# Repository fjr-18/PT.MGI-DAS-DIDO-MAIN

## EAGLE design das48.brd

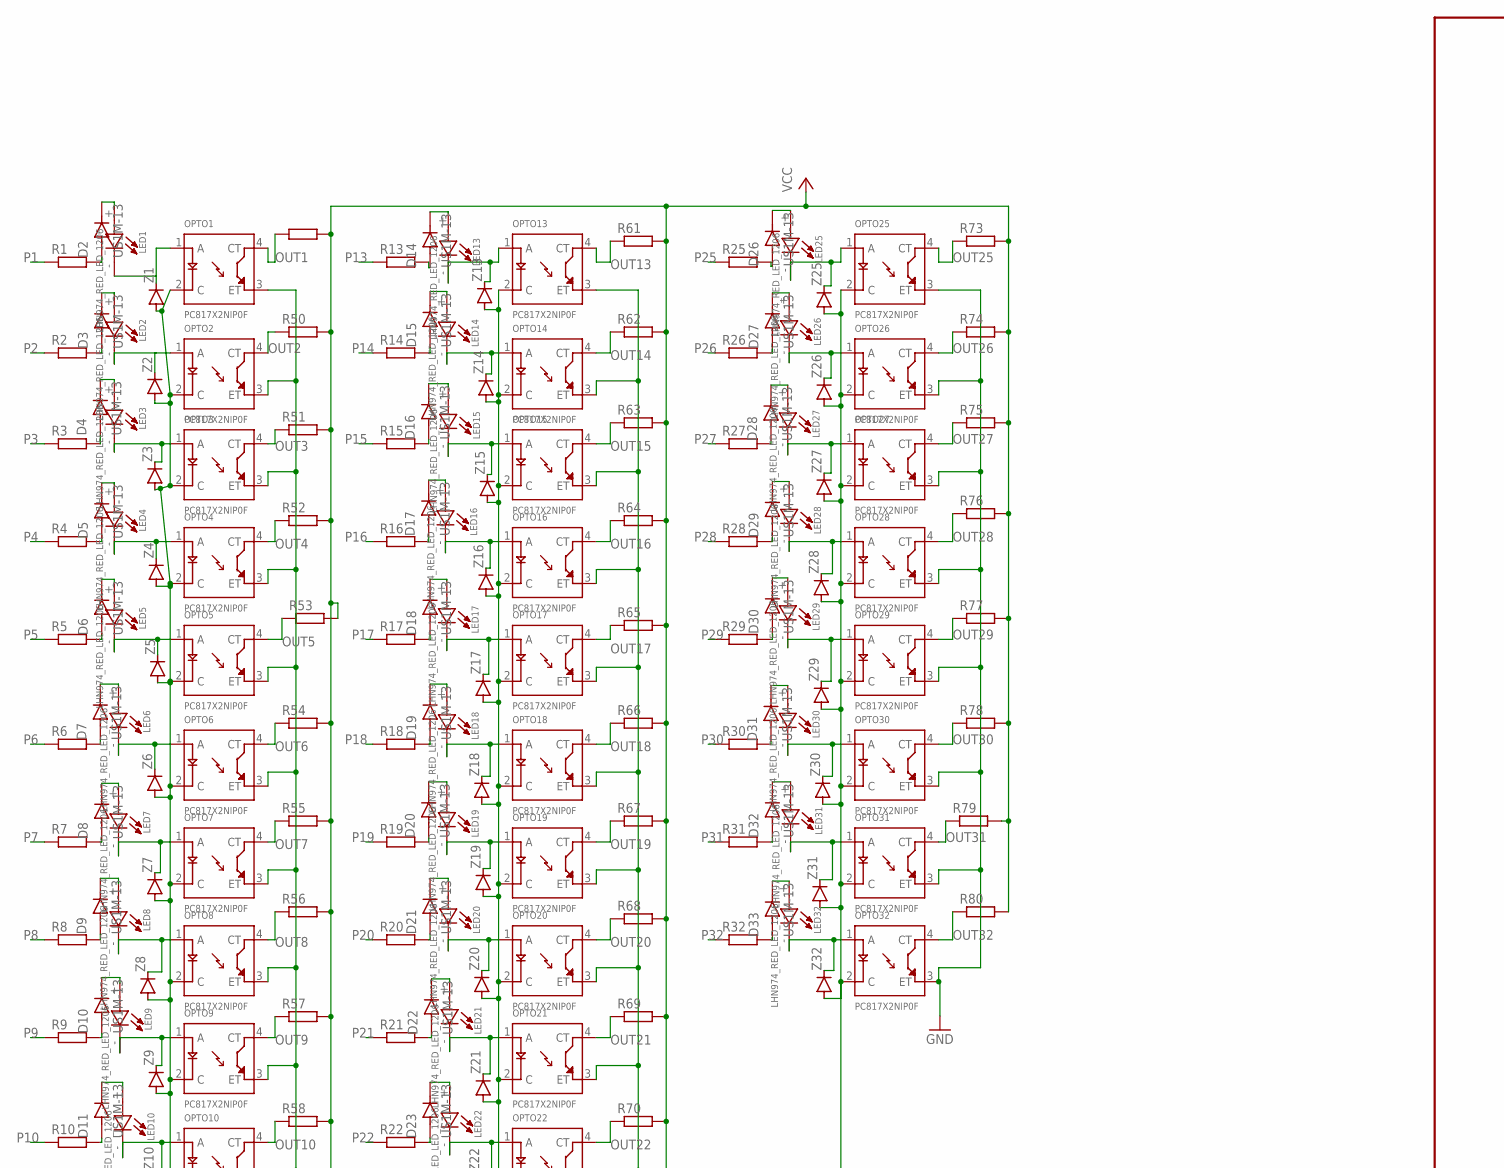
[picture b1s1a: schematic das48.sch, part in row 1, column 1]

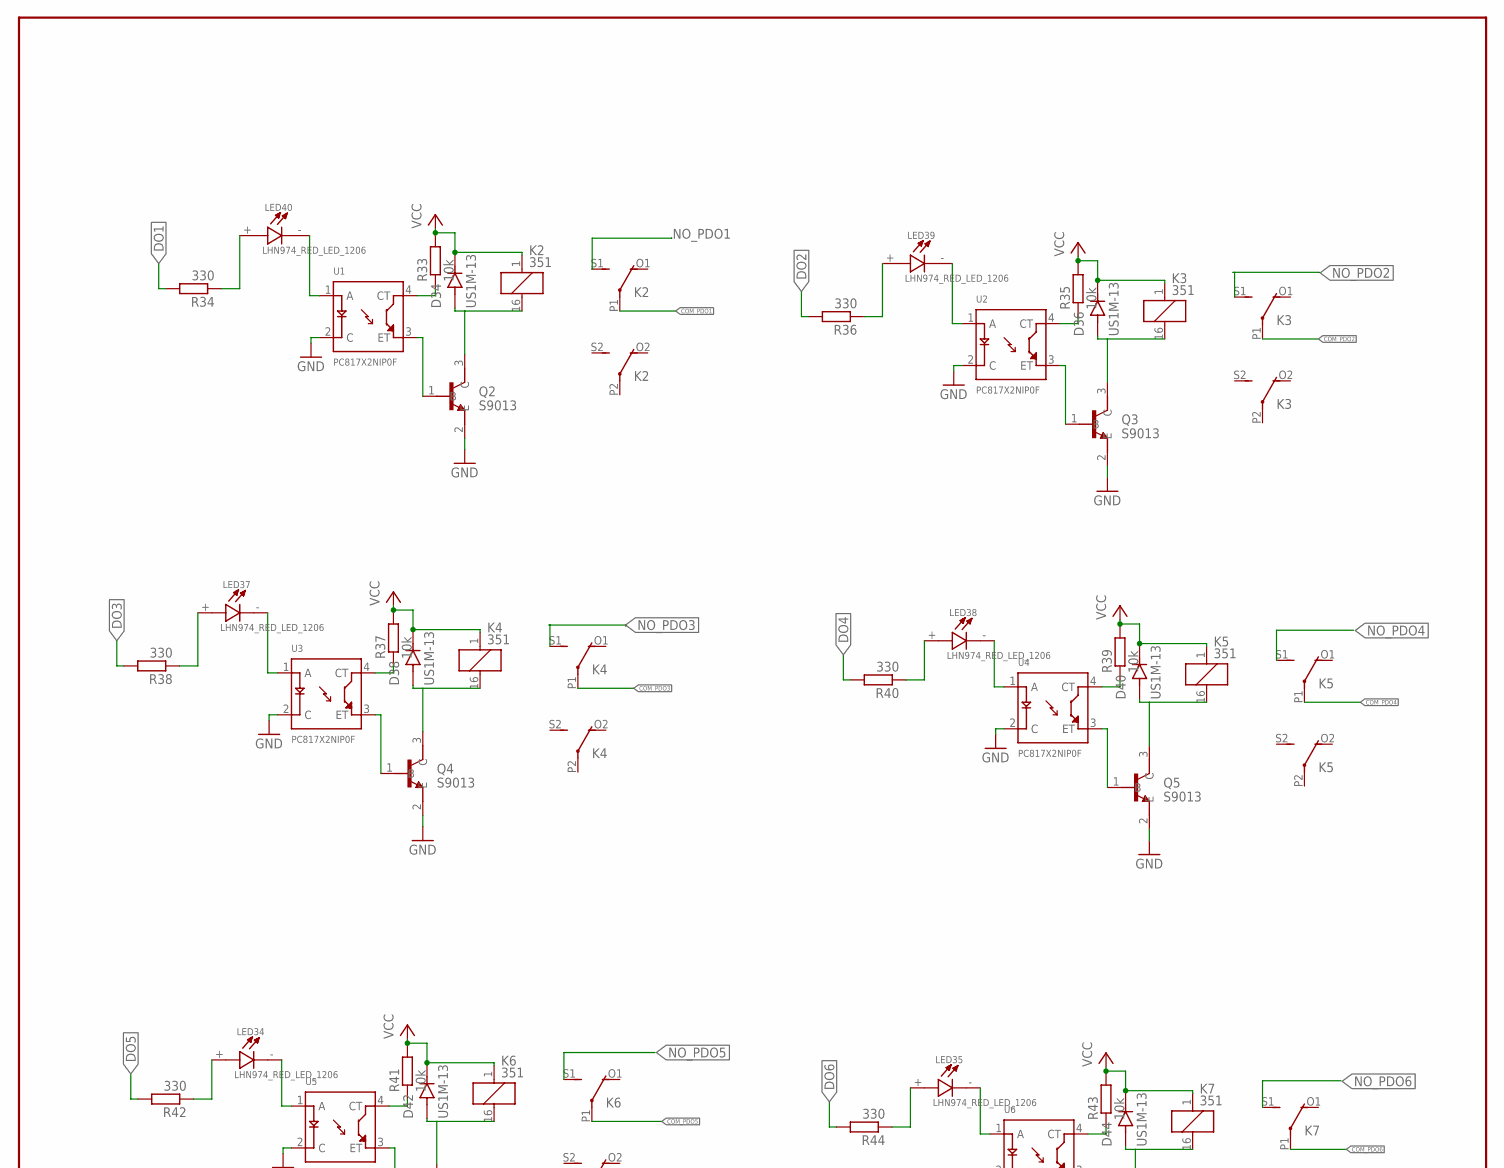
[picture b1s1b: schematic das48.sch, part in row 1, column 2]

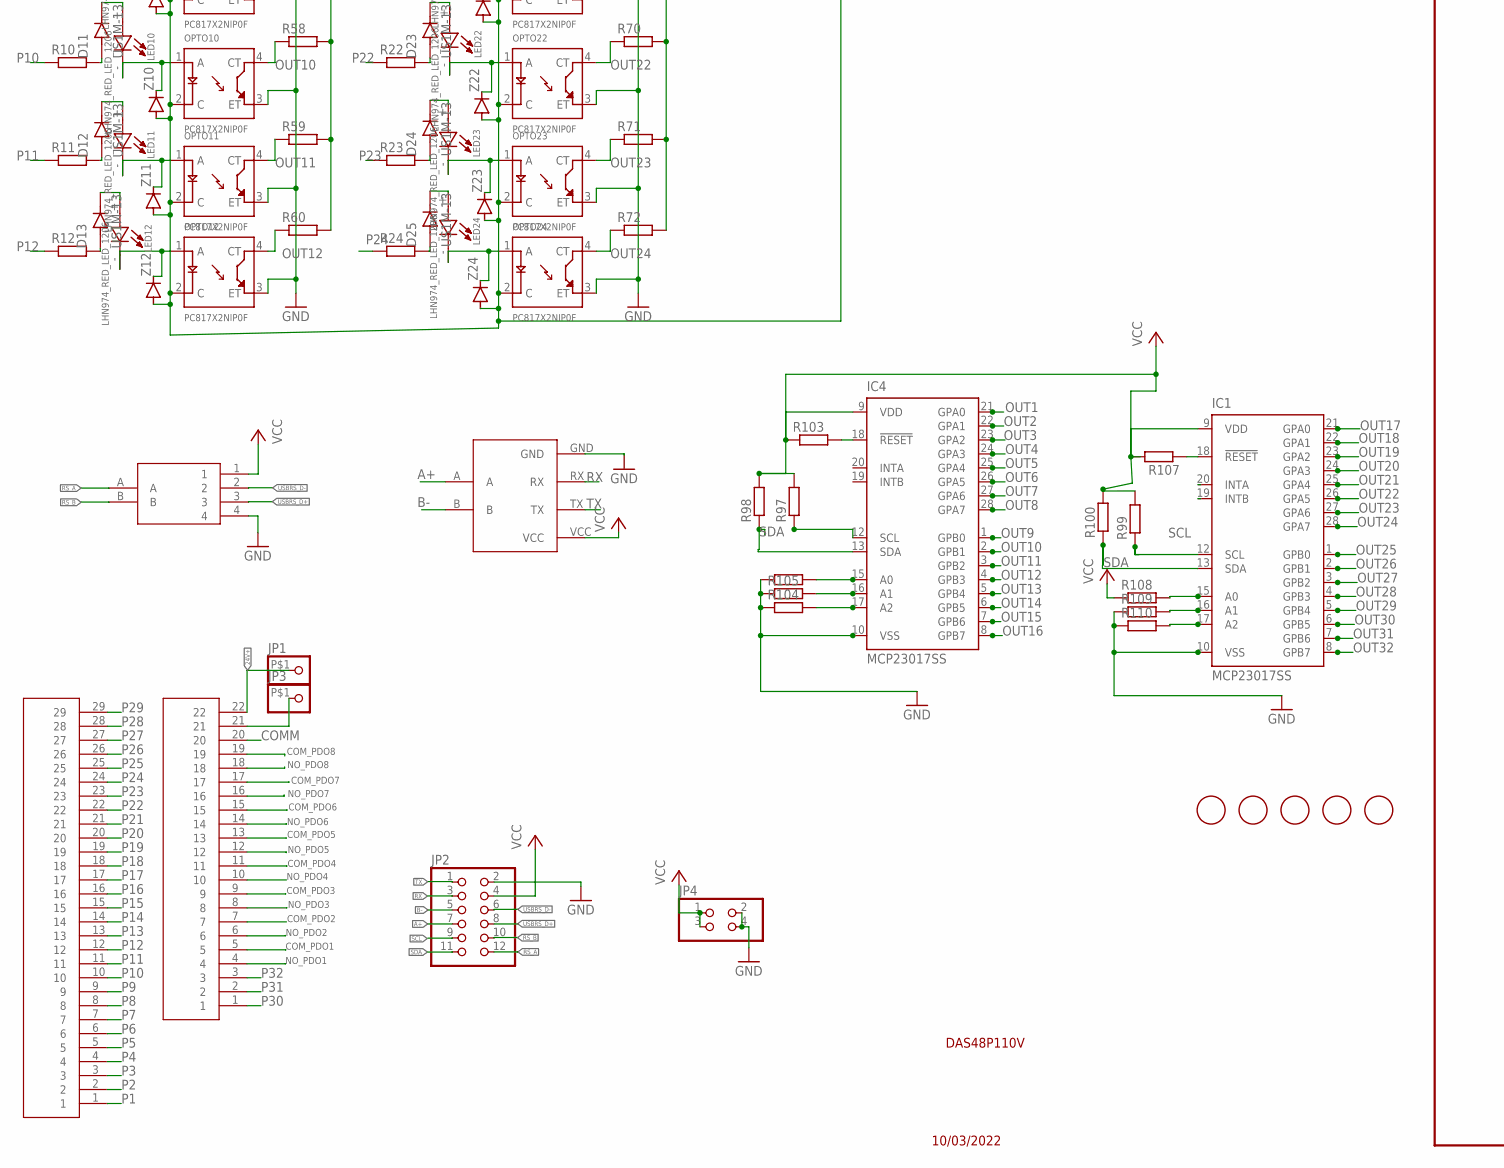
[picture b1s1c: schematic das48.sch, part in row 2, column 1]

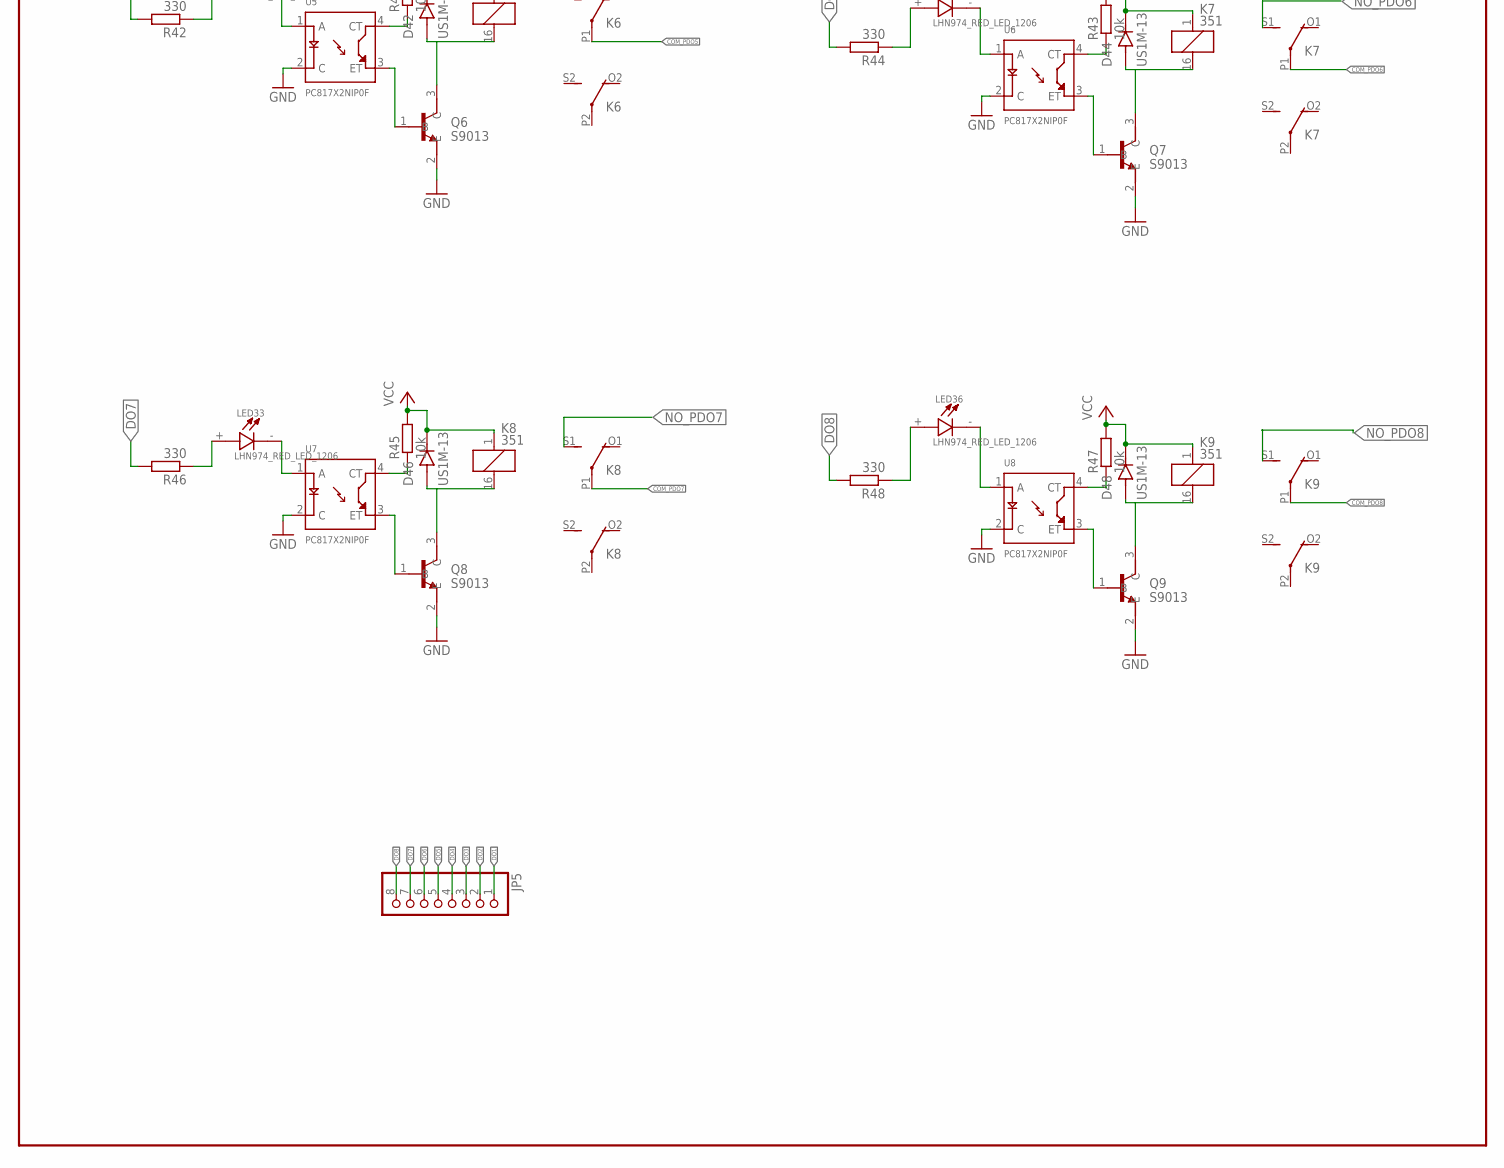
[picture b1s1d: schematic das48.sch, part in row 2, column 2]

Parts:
D2, D3, D4, D5, D6, D7, D8, D9, D10, D11, D12, D13, D14, D15, D16, D17, D18, D19, D20, D21, D22, D23, D24, D25, D26, D27, D28, D29, D30, D31, D32, D33, D34, D36, D38, D40, D42, D44, D46, D48: US1M-13; DIOM5226X240N
HEADER-22P1: HEADER-22P; HEADER-29P
HEADER-29P1: HEADER-29P
IC1, IC4: MCP23017SS; SSOP28DB
JP1, JP3: PINHD-1X1-BIGPOGO; 1X1-BIGPOGO
JP2: PINHD-2X6; 2X06
JP4: PINHD-2X2; 2X02
JP5: PINHD-1X8; 1X08
K2, K3, K4, K5, K6, K7, K8, K9: 351
LED1, LED2, LED3, LED4, LED5, LED6, LED7, LED8, LED9, LED10, LED11, LED12, LED13, LED14, LED15, LED16, LED17, LED18, LED19, LED20, LED21, LED22, LED23, LED24, LED25, LED26, LED27, LED28, LED29, LED30, LED31, LED32, LED33, LED34, LED35, LED36, LED37, LED38, LED39, LED40: LHN974_RED_LED_1206; LEDC3216X120N
OPTO1, OPTO2, OPTO3, OPTO4, OPTO5, OPTO6, OPTO7, OPTO8, OPTO9, OPTO10, OPTO11, OPTO12, OPTO13, OPTO14, OPTO15, OPTO16, OPTO17, OPTO18, OPTO19, OPTO20, OPTO21, OPTO22, OPTO23, OPTO24, OPTO25, OPTO26, OPTO27, OPTO28, OPTO29, OPTO30, OPTO31, OPTO32: PC817X2NIP0F; SOT254P975X400-4N
Q2, Q3, Q4, Q5, Q6, Q7, Q8, Q9: S9013; SOT95P240X120-3N
R1, R2, R3, R4, R5, R6, R7, R8, R9, R10, R11, R12, R13, R14, R15, R16, R17, R18, R19, R20, R21, R22, R23, R24, R25, R26, R27, R28, R29, R30, R31, R32: R-EU_0617/17; 0617/17
R33, R35, R37, R39, R41, R43, R45, R47: 10k; R0805
R34, R36, R38, R40, R42, R44, R46, R48: 330; R0805
R49, R50, R51, R52, R53, R54, R55, R56, R57, R58, R59, R60, R61, R62, R63, R64, R65, R66, R67, R68, R69, R70, R71, R72, R73, R74, R75, R76, R77, R78, R79, R80, R97, R98, R99, R100, R103, R104, R105, R106, R107, R108, R109, R110: R-EU_R0805; R0805
TTL-RS1: TTL-RS485
U1, U2, U3, U4, U5, U6, U7, U8: PC817X2NIP0F; SOT254P975X400-4N
U$1, U$2, U$3, U$4, U$5: FIDUCIAL; FIDUCIAL_1MM
USB2RS1: USB2RS485
Z1, Z2, Z3, Z4, Z5, Z6, Z7, Z8, Z9, Z10, Z11, Z12, Z13, Z14, Z15, Z16, Z17, Z18, Z19, Z20, Z21, Z22, Z23, Z24, Z25, Z26, Z27, Z28, Z29, Z30, Z31, Z32: DIODE-SOD123; SOD123

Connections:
24V+: HEADER-22P1.22, JP1.P$1
A+: JP2.7, TTL-RS1.A
B-: JP2.5, TTL-RS1.B
COMM: HEADER-22P1.20, OPTO1.2 (C), OPTO2.2 (C), OPTO3.2 (C), OPTO4.2 (C), OPTO5.2 (C), OPTO6.2 (C), OPTO7.2 (C), OPTO8.2 (C), OPTO9.2 (C), OPTO10.2 (C), OPTO11.2 (C), OPTO12.2 (C), OPTO13.2 (C), OPTO14.2 (C), OPTO15.2 (C), OPTO16.2 (C), OPTO17.2 (C), OPTO18.2 (C), OPTO19.2 (C), OPTO20.2 (C), OPTO21.2 (C), OPTO22.2 (C), OPTO23.2 (C), OPTO24.2 (C), OPTO25.2 (C), OPTO26.2 (C), OPTO27.2 (C), OPTO28.2 (C), OPTO29.2 (C), OPTO30.2 (C), OPTO31.2 (C), OPTO32.2 (C), Z1.A, Z2.A, Z3.A, Z4.A, Z5.A, Z6.A, Z7.A, Z8.A, Z9.A, Z10.A, Z11.A, Z12.A, Z13.A, Z14.A, Z15.A, Z16.A, Z17.A, Z18.A, Z19.A, Z20.A, Z21.A, Z22.A, Z23.A, Z24.A, Z25.A, Z26.A, Z27.A, Z28.A, Z29.A, Z30.A, Z31.A, Z32.A
COM_PDO1: HEADER-22P1.5, K2.P1
COM_PDO2: HEADER-22P1.7, K3.P1
COM_PDO3: HEADER-22P1.9, K4.P1
COM_PDO4: HEADER-22P1.11, K5.P1
COM_PDO5: HEADER-22P1.13, K6.P1
COM_PDO6: HEADER-22P1.15, K7.P1
COM_PDO7: HEADER-22P1.17, K8.P1
COM_PDO8: HEADER-22P1.19, K9.P1
DO1: JP5.1, R34.2
DO2: JP5.2, R36.2
DO3: JP5.3, R38.2
DO4: JP5.4, R40.2
DO5: JP5.5, R42.2
DO6: JP5.6, R44.2
DO7: JP5.7, R46.2
DO8: JP5.8, R48.2
GND: IC1.10 (VSS), IC4.10 (VSS), JP2.2, JP4.2, JP4.4, OPTO1.3 (ET), OPTO2.3 (ET), OPTO3.3 (ET), OPTO4.3 (ET), OPTO5.3 (ET), OPTO6.3 (ET), OPTO7.3 (ET), OPTO8.3 (ET), OPTO9.3 (ET), OPTO10.3 (ET), OPTO11.3 (ET), OPTO12.3 (ET), OPTO13.3 (ET), OPTO14.3 (ET), OPTO15.3 (ET), OPTO16.3 (ET), OPTO17.3 (ET), OPTO18.3 (ET), OPTO19.3 (ET), OPTO20.3 (ET), OPTO21.3 (ET), OPTO22.3 (ET), OPTO23.3 (ET), OPTO24.3 (ET), OPTO25.3 (ET), OPTO26.3 (ET), OPTO27.3 (ET), OPTO28.3 (ET), OPTO29.3 (ET), OPTO30.3 (ET), OPTO31.3 (ET), OPTO32.3 (ET), Q2.2 (E), Q3.2 (E), Q4.2 (E), Q5.2 (E), Q6.2 (E), Q7.2 (E), Q8.2 (E), Q9.2 (E), R104.1, R105.1, R106.1, R109.1, R110.1, TTL-RS1.GND, U1.2 (C), U2.2 (C), U3.2 (C), U4.2 (C), U5.2 (C), U6.2 (C), U7.2 (C), U8.2 (C), USB2RS1.4
unnamed: D2.A, R1.2
unnamed: D2.C (K), LED1.+
unnamed: D3.A, R2.2
unnamed: D3.C (K), LED2.+
unnamed: D4.A, R3.2
unnamed: D4.C (K), LED3.+
unnamed: D5.A, R4.2
unnamed: D5.C (K), LED4.+
unnamed: D6.A, R5.2
unnamed: D6.C (K), LED5.+
unnamed: D7.A, R6.2
unnamed: D7.C (K), LED6.+
unnamed: D8.A, R7.2
unnamed: D8.C (K), LED7.+
unnamed: D9.A, R8.2
unnamed: D9.C (K), LED8.+
unnamed: D15.A, R14.2
unnamed: LED1.-, OPTO1.1 (A), Z1.C
unnamed: LED13.-, OPTO13.1 (A), Z13.C
unnamed: D10.A, R9.2
unnamed: LED14.-, OPTO14.1 (A), Z14.C
unnamed: D10.C (K), LED9.+
unnamed: LED15.-, OPTO15.1 (A), Z15.C
unnamed: D11.A, R10.2
unnamed: LED16.-, OPTO16.1 (A), Z16.C
unnamed: D11.C (K), LED10.+
unnamed: LED17.-, OPTO17.1 (A), Z17.C
unnamed: D12.A, R11.2
unnamed: LED18.-, OPTO18.1 (A), Z18.C
unnamed: D12.C (K), LED11.+
unnamed: LED19.-, OPTO19.1 (A), Z19.C
unnamed: LED20.-, OPTO20.1 (A), Z20.C
unnamed: LED21.-, OPTO21.1 (A), Z21.C
unnamed: D15.C (K), LED14.+
unnamed: LED22.-, OPTO22.1 (A), Z22.C
unnamed: D13.A, R12.2
unnamed: LED23.-, OPTO23.1 (A), Z23.C
unnamed: D13.C (K), LED12.+
unnamed: LED24.-, OPTO24.1 (A), Z24.C
unnamed: D14.A, R13.2
unnamed: LED25.-, OPTO25.1 (A), Z25.C
unnamed: D14.C (K), LED13.+
unnamed: LED26.-, OPTO26.1 (A), Z26.C
unnamed: D16.A, R15.2
unnamed: LED27.-, OPTO27.1 (A), Z27.C
unnamed: D16.C (K), LED15.+
unnamed: LED28.-, OPTO28.1 (A), Z28.C
unnamed: D17.A, R16.2
unnamed: LED29.-, OPTO29.1 (A), Z29.C
unnamed: D17.C (K), LED16.+
unnamed: LED30.-, OPTO30.1 (A), Z30.C
unnamed: D18.A, R17.2
unnamed: LED31.-, OPTO31.1 (A), Z31.C
unnamed: D18.C (K), LED17.+
unnamed: LED32.-, OPTO32.1 (A), Z32.C
unnamed: D19.A, R18.2
unnamed: LED40.+, R34.1
unnamed: D19.C (K), LED18.+
unnamed: D34.A, K2.16 (2), Q2.3 (C)
unnamed: D20.A, R19.2
unnamed: LED39.+, R36.1
unnamed: D20.C (K), LED19.+
unnamed: R33.1, U1.4 (CT)
unnamed: D32.A, R31.2
unnamed: Q2.1 (B), U1.3 (ET)
unnamed: D21.A, R20.2
unnamed: LED37.+, R38.1
unnamed: D21.C (K), LED20.+
unnamed: D36.A, K3.16 (2), Q3.3 (C)
unnamed: LED38.+, R40.1
unnamed: D22.A, R21.2
unnamed: R35.1, U2.4 (CT)
unnamed: D22.C (K), LED21.+
unnamed: Q3.1 (B), U2.3 (ET)
unnamed: LED34.+, R42.1
unnamed: D23.A, R22.2
unnamed: D38.A, K4.16 (2), Q4.3 (C)
unnamed: D23.C (K), LED22.+
unnamed: LED35.+, R44.1
unnamed: D24.A, R23.2
unnamed: R37.1, U3.4 (CT)
unnamed: D24.C (K), LED23.+
unnamed: Q4.1 (B), U3.3 (ET)
unnamed: D25.A, R24.2
unnamed: LED33.+, R46.1
unnamed: LED2.-, OPTO2.1 (A), Z2.C
unnamed: LED3.-, OPTO3.1 (A), Z3.C
unnamed: LED4.-, OPTO4.1 (A), Z4.C
unnamed: LED5.-, OPTO5.1 (A), Z5.C
unnamed: LED6.-, OPTO6.1 (A), Z6.C
unnamed: LED7.-, OPTO7.1 (A), Z7.C
unnamed: LED8.-, OPTO8.1 (A), Z8.C
unnamed: LED9.-, OPTO9.1 (A), Z9.C
unnamed: LED10.-, OPTO10.1 (A), Z10.C
unnamed: LED11.-, OPTO11.1 (A), Z11.C
unnamed: LED12.-, OPTO12.1 (A), Z12.C
unnamed: LED40.-, U1.1 (A)
unnamed: LED39.-, U2.1 (A)
unnamed: LED37.-, U3.1 (A)
unnamed: D40.A, K5.16 (2), Q5.3 (C)
unnamed: LED38.-, U4.1 (A)
unnamed: LED34.-, U5.1 (A)
unnamed: LED36.+, R48.1
unnamed: D25.C (K), LED24.+
unnamed: D26.A, R25.2
unnamed: D26.C (K), LED25.+
unnamed: IC1.15 (A0), R108.2
unnamed: IC1.16 (A1), R109.2
unnamed: IC4.15 (A0), R106.2
unnamed: IC4.16 (A1), R105.2
unnamed: IC4.17 (A2), R104.2
unnamed: R39.1, U4.4 (CT)
unnamed: IC1.17 (A2), R110.2
unnamed: D27.A, R26.2
unnamed: D27.C (K), LED26.+
unnamed: D28.A, R27.2
unnamed: D28.C (K), LED27.+
unnamed: D32.C (K), LED31.+
unnamed: D29.A, R28.2
unnamed: D29.C (K), LED28.+
unnamed: D30.C (K), LED29.+
unnamed: D30.A, R29.2
unnamed: D31.A, R30.2
unnamed: D31.C (K), LED30.+
unnamed: D33.C (K), LED32.+
unnamed: D33.A, R32.2
unnamed: Q5.1 (B), U4.3 (ET)
unnamed: IC4.18 (!RESET), R103.2
unnamed: D42.A, K6.16 (2), Q6.3 (C)
unnamed: IC1.18 (!RESET), R107.1
unnamed: R41.1, U5.4 (CT)
unnamed: Q6.1 (B), U5.3 (ET)
unnamed: LED35.-, U6.1 (A)
unnamed: D44.A, K7.16 (2), Q7.3 (C)
unnamed: LED33.-, U7.1 (A)
unnamed: R43.1, U6.4 (CT)
unnamed: Q7.1 (B), U6.3 (ET)
unnamed: LED36.-, U8.1 (A)
unnamed: D46.A, K8.16 (2), Q8.3 (C)
unnamed: R45.1, U7.4 (CT)
unnamed: Q8.1 (B), U7.3 (ET)
unnamed: D48.A, K9.16 (2), Q9.3 (C)
unnamed: R47.1, U8.4 (CT)
unnamed: Q9.1 (B), U8.3 (ET)
unnamed: HEADER-22P1.21, JP3.P$1
NO_PDO1: HEADER-22P1.4, K2.S1 (S)
NO_PDO2: HEADER-22P1.6, K3.S1 (S)
NO_PDO3: HEADER-22P1.8, K4.S1 (S)
NO_PDO4: HEADER-22P1.10, K5.S1 (S)
NO_PDO5: HEADER-22P1.12, K6.S1 (S)
NO_PDO6: HEADER-22P1.14, K7.S1 (S)
NO_PDO7: HEADER-22P1.16, K8.S1 (S)
NO_PDO8: HEADER-22P1.18, K9.S1 (S)
OUT1: IC4.21 (GPA0), OPTO1.4 (CT), R49.1
OUT2: IC4.22 (GPA1), OPTO2.4 (CT), R50.1
OUT3: IC4.23 (GPA2), OPTO3.4 (CT), R51.1
OUT4: IC4.24 (GPA3), OPTO4.4 (CT), R52.1
OUT5: IC4.25 (GPA4), OPTO5.4 (CT), R53.1
OUT6: IC4.26 (GPA5), OPTO6.4 (CT), R54.1
OUT7: IC4.27 (GPA6), OPTO7.4 (CT), R55.1
OUT8: IC4.28 (GPA7), OPTO8.4 (CT), R56.1
OUT9: IC4.1 (GPB0), OPTO9.4 (CT), R57.1
OUT10: IC4.2 (GPB1), OPTO10.4 (CT), R58.1
OUT11: IC4.3 (GPB2), OPTO11.4 (CT), R59.1
OUT12: IC4.4 (GPB3), OPTO12.4 (CT), R60.1
OUT13: IC4.5 (GPB4), OPTO13.4 (CT), R61.1
OUT14: IC4.6 (GPB5), OPTO14.4 (CT), R62.1
OUT15: IC4.7 (GPB6), OPTO15.4 (CT), R63.1
OUT16: IC4.8 (GPB7), OPTO16.4 (CT), R64.1
OUT17: IC1.21 (GPA0), OPTO17.4 (CT), R65.1
OUT18: IC1.22 (GPA1), OPTO18.4 (CT), R66.1
OUT19: IC1.23 (GPA2), OPTO19.4 (CT), R67.1
OUT20: IC1.24 (GPA3), OPTO20.4 (CT), R68.1
OUT21: IC1.25 (GPA4), OPTO21.4 (CT), R69.1
OUT22: IC1.26 (GPA5), OPTO22.4 (CT), R70.1
OUT23: IC1.27 (GPA6), OPTO23.4 (CT), R71.1
OUT24: IC1.28 (GPA7), OPTO24.4 (CT), R72.1
OUT25: IC1.1 (GPB0), OPTO25.4 (CT), R73.1
OUT26: IC1.2 (GPB1), OPTO26.4 (CT), R74.1
OUT27: IC1.3 (GPB2), OPTO27.4 (CT), R75.1
OUT28: IC1.4 (GPB3), OPTO28.4 (CT), R76.1
OUT29: IC1.5 (GPB4), OPTO29.4 (CT), R77.1
OUT30: IC1.6 (GPB5), OPTO30.4 (CT), R78.1
OUT31: IC1.7 (GPB6), OPTO31.4 (CT), R79.1
OUT32: IC1.8 (GPB7), OPTO32.4 (CT), R80.1
P1: HEADER-29P1.1, R1.1
P2: HEADER-29P1.2, R2.1
P3: HEADER-29P1.3, R3.1
P4: HEADER-29P1.4, R4.1
P5: HEADER-29P1.5, R5.1
P6: HEADER-29P1.6, R6.1
P7: HEADER-29P1.7, R7.1
P8: HEADER-29P1.8, R8.1
P9: HEADER-29P1.9, R9.1
P10: HEADER-29P1.10, R10.1
P11: HEADER-29P1.11, R11.1
P12: HEADER-29P1.12, R12.1
P13: HEADER-29P1.13, R13.1
P14: HEADER-29P1.14, R14.1
P15: HEADER-29P1.15, R15.1
P16: HEADER-29P1.16, R16.1
P17: HEADER-29P1.17, R17.1
P18: HEADER-29P1.18, R18.1
P19: HEADER-29P1.19, R19.1
P20: HEADER-29P1.20, R20.1
P21: HEADER-29P1.21, R21.1
P22: HEADER-29P1.22, R22.1
P23: HEADER-29P1.23, R23.1
P24: HEADER-29P1.24, R24.1
P25: HEADER-29P1.25, R25.1
P26: HEADER-29P1.26, R26.1
P27: HEADER-29P1.27, R27.1
P28: HEADER-29P1.28, R28.1
P29: HEADER-29P1.29, R29.1
P30: HEADER-22P1.1, R30.1
P31: HEADER-22P1.2, R31.1
P32: HEADER-22P1.3, R32.1
RS_A: JP2.12, USB2RS1.A
RS_B: JP2.10, USB2RS1.B
RX: JP2.3, TTL-RS1.RX
SCL: IC1.12 (SCL), IC4.12 (SCL), JP2.9, R97.1, R99.1
SDA: IC1.13 (SDA), IC4.13 (SDA), JP2.11, R98.1, R100.1
TX: JP2.1, TTL-RS1.TX
USBRS_D+: JP2.8, USB2RS1.3
USBRS_D-: JP2.6, USB2RS1.2
VCC: D34.C (K), D36.C (K), D38.C (K), D40.C (K), D42.C (K), D44.C (K), D46.C (K), D48.C (K), IC1.9 (VDD), IC4.9 (VDD), JP2.4, JP4.1, JP4.3, K2.1, K3.1, K4.1, K5.1, K6.1, K7.1, K8.1, K9.1, R33.2, R35.2, R37.2, R39.2, R41.2, R43.2, R45.2, R47.2, R49.2, R50.2, R51.2, R52.2, R53.2, R54.2, R55.2, R56.2, R57.2, R58.2, R59.2, R60.2, R61.2, R62.2, R63.2, R64.2, R65.2, R66.2, R67.2, R68.2, R69.2, R70.2, R71.2, R72.2, R73.2, R74.2, R75.2, R76.2, R77.2, R78.2, R79.2, R80.2, R97.2, R98.2, R99.2, R100.2, R103.1, R107.2, R108.1, TTL-RS1.VCC, USB2RS1.1

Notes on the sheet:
DAS48P110V
10/03/2022

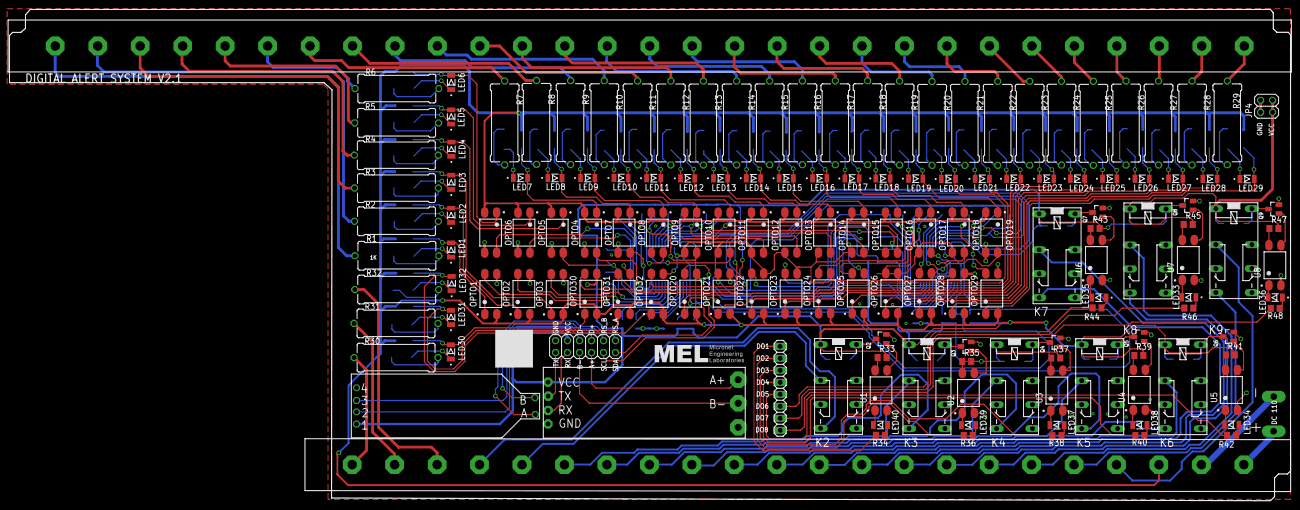
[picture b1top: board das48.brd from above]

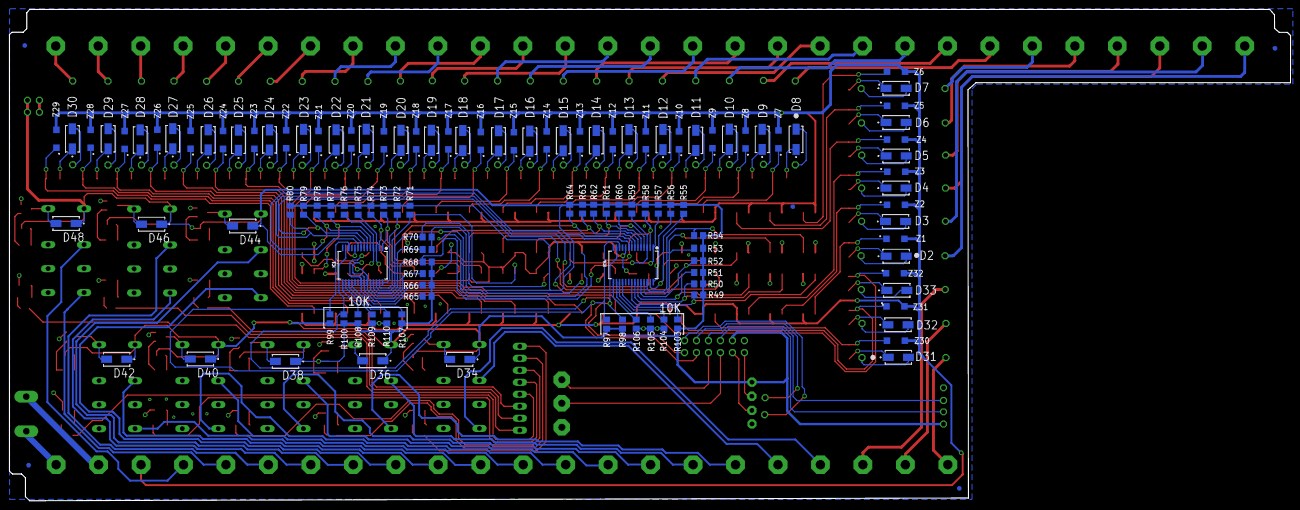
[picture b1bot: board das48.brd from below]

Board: 2 copper layers, 271.5 x 104.1 mm, 276 parts (123 on the bottom side), 247 nets.

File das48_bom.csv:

Comment,Designator,Footprint,LCSC Part #
,JP1,1X1-BIGPOGO,
,JP3,1X1-BIGPOGO,
,JP5,1X08,
,JP4,2X02,
,JP2,2X06,
,R1,0617/17,
,R2,0617/17,
,R3,0617/17,
,R4,0617/17,
,R5,0617/17,
,R6,0617/17,
,R7,0617/17,
,R8,0617/17,
,R9,0617/17,
,R10,0617/17,
,R11,0617/17,
,R12,0617/17,
,R13,0617/17,
,R14,0617/17,
,R15,0617/17,
,R16,0617/17,
,R17,0617/17,
,R18,0617/17,
,R19,0617/17,
,R20,0617/17,
,R21,0617/17,
,R22,0617/17,
,R23,0617/17,
,R24,0617/17,
,R25,0617/17,
,R26,0617/17,
,R27,0617/17,
,R28,0617/17,
,R29,0617/17,
,R30,0617/17,
,R31,0617/17,
,R32,0617/17,
,HEADER-22P1,HEADER-29P,
,HEADER-29P1,HEADER-29P,
,R49,R0805,
,R50,R0805,
,R51,R0805,
,R52,R0805,
,R53,R0805,
,R54,R0805,
,R55,R0805,
,R56,R0805,
,R57,R0805,
,R58,R0805,
,R59,R0805,
,R60,R0805,
,R61,R0805,
,R62,R0805,
,R63,R0805,
,R64,R0805,
,R65,R0805,
,R66,R0805,
,R67,R0805,
,R68,R0805,
,R69,R0805,
,R70,R0805,
,R71,R0805,
,R72,R0805,
,R73,R0805,
,R74,R0805,
,R75,R0805,
,R76,R0805,
,R77,R0805,
,R78,R0805,
,R79,R0805,
,R80,R0805,
,R97,R0805,
,R98,R0805,
,R99,R0805,
,R100,R0805,
,R103,R0805,
,R104,R0805,
,R105,R0805,
,R106,R0805,
,R107,R0805,
,R108,R0805,
,R109,R0805,
,R110,R0805,
,Z1,SOD123,
,Z2,SOD123,
,Z3,SOD123,
,Z4,SOD123,
,Z5,SOD123,
,Z6,SOD123,
,Z7,SOD123,
,Z8,SOD123,
,Z9,SOD123,
,Z10,SOD123,
,Z11,SOD123,
,Z12,SOD123,
,Z13,SOD123,
,Z14,SOD123,
,Z15,SOD123,
,Z16,SOD123,
,Z17,SOD123,
,Z18,SOD123,
,Z19,SOD123,
,Z20,SOD123,
,Z21,SOD123,
,Z22,SOD123,
,Z23,SOD123,
,Z24,SOD123,
,Z25,SOD123,
,Z26,SOD123,
,Z27,SOD123,
,Z28,SOD123,
,Z29,SOD123,
,Z30,SOD123,
,Z31,SOD123,
,Z32,SOD123,
,TTL-RS1,TTL-RS485,
,USB2RS1,USB2RS485,
10k,R33 R35 R37 R39 R41 R43 R45 R47,R0805,
330,R34 R36 R38 R40 R42 R44 R46 R48,R0805,
351,K2 K3 K4 K5 K6 K7 K8 K9,351,
FIDUCIAL,U$1 U$2 U$3 U$4 U$5,FIDUCIAL_1MM,
LHN974_RED_LED_1206,LED1 LED2 LED3 LED4 LED5 LED6 LED7 LED8 LED9 LED10 LED11 LED12 LED13 LED14 LED15 LED16 LED17 LED18 LED19 LED20 LED21 LED22 LED23 LED24 LED25 LED26 LED27 LED28 LED29 LED30 LED31 LED32 LED33 LED34 LED35 LED36 LED37 LED38 LED39 LED40,LEDC3216X120N,
MCP23017SS,IC1 IC4,SSOP28DB,
PC817X2NIP0F,OPTO1 OPTO2 OPTO3 OPTO4 OPTO5 OPTO6 OPTO7 OPTO8 OPTO9 OPTO10 OPTO11 OPTO12 OPTO13 OPTO14 OPTO15 OPTO16 OPTO17 OPTO18 OPTO19 OPTO20 OPTO21 OPTO22 OPTO23 OPTO24 OPTO25 OPTO26 OPTO27 OPTO28 OPTO29 OPTO30 OPTO31 OPTO32 U1 U2 U3 U4 U5 U6 U7 U8,SOT254P975X400-4N,
S9013,Q2 Q3 Q4 Q5 Q6 Q7 Q8 Q9,SOT95P240X120-3N,
US1M-13,D2 D3 D4 D5 D6 D7 D8 D9 D10 D11 D12 D13 D14 D15 D16 D17 D18 D19 D20 D21 D22 D23 D24 D25 D26 D27 D28 D29 D30 D31 D32 D33 D34 D36 D38 D40 D42 D44 D46 D48,DIOM5226X240N,
